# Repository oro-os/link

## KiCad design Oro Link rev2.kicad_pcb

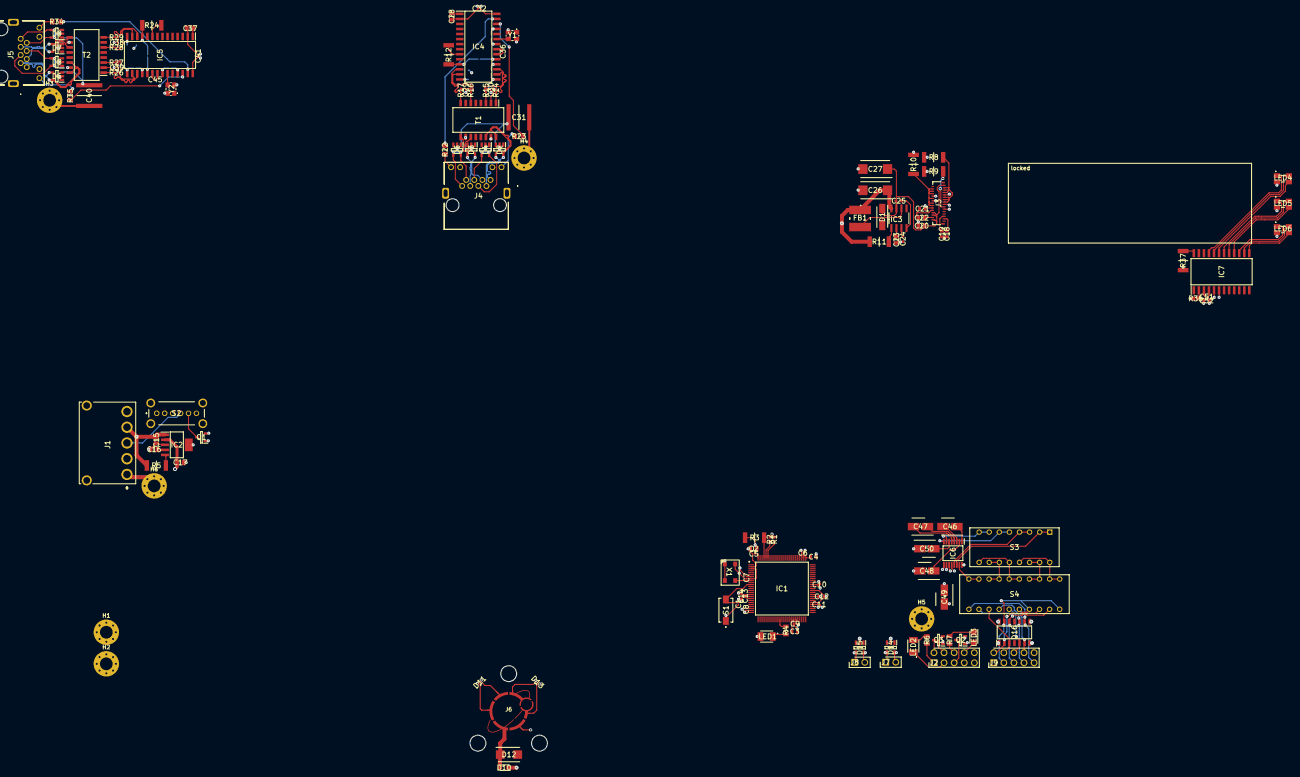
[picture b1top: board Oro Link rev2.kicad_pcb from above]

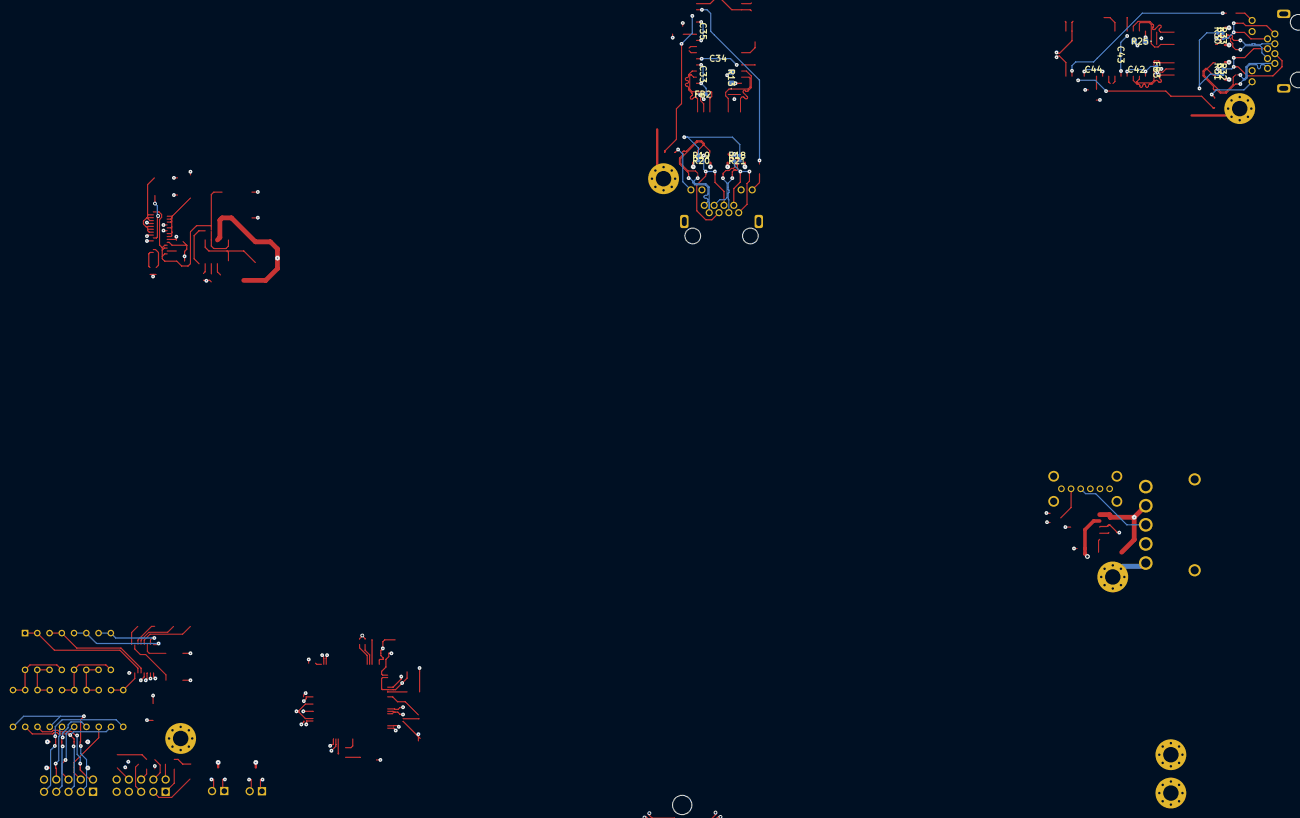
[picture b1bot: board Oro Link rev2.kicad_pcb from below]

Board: 4 copper layers, 148 parts (18 on the bottom side), 148 nets.

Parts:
C1, C5, C6, C7, C8, C9, C10, C11, C13, C29, C30, C32, C33, C34, C35, C36, C38, C39, C41, C42, C43, C44, C45, C51: 0.1u; CAPC0402X22N
C2, C20: 4.7u; CAPC2012X135N
C3, C4, C12: 2.2u; CAPC1608X90N
C14, C18, C19, C21, C52: 1u; CAPC1608X90N
C15, C16, C17, C28, C37: 10u; CAPC2012X135N
C22: 4,7u; CAPC2012X135N
C23: 0.01u; CAPC2012X75N
C24: 0.047u; C1608_Commercial_Tight
C25: 0.001u; C1608_Commercial_Tight
C26, C27: 33u; CAPPM7343X310N
C31, C40: 1nF 5kV; CAPC5664X270N
C46, C47, C48, C49, C50: 0.1u; CAPAE430X610N
D1: SS12; DIOM5227X250N
D2, D3, D4, D5, D6, D7, D8, D9, D14, D15: ESDS302DBVR; SOT95P280X145-5N
D10: RFU02VSM8STR; SODFL2514X80N
D11, D13: RCLAMP3552T.TNT; RCLAMP3552TTNT
D12: P6SMB15A-Q; DIOM5436X244N
D16: SMDA05C-8.TBT; SOIC127P600X175-14N
FB1: CD54NP-180MC; CD54NP180MC
FB2, FB3: BLM18BB600SZ1D; BLM18EG121SH1D
H1, H2, H3, H4, H5, H6: MountingHole_Pad; MountingHole_3.2mm_M3_Pad_Via
IC1: STM32F479VGT6; QFP50P1600X1600X160-100N
IC2: TPS73733DCQ; SOT127P706X180-6N
IC3: TPS6734IDR; SOIC127P600X175-8N
IC4, IC5: ENC28J60-I_SO; SOIC127P1030X265-28N
IC6: SN75C3232EPWR; SOP65P640X120-16N
IC7: IS31FL3218-GRLS2; SOIC127P1036X265-24N
J1: DF63-5P-3.96DS; DF635P396DS
J2, J9: 67996-110HLF; HDRV10W67P254_2X5_1270X483X858P
J3: 3-2328724-1; 323287241
J4, J5: SS-60300-103; SS60300103
J6: OroConn6p; OroConn6p_WithMounts
J7, J8: 10129378-902003BLF; HDRV2W67P0X254_1X2_508X241X1082P
LED1, LED2: AA3528VRVFS/A; AA3528VRVFSA
LED3: CLM3C-WKW-CXAYA453; CLM3CWKWCXAYA453
LED4, LED5, LED6: 150120M173000
Q1, Q2, Q3: PMV20ENR; SOT95P230X110-3N
R1, R2: 4.7k; RESC1005X40N
R3, R5, R8, R9, R10, R11, R12, R24, R37: 10k; RESC5025X65N
R4, R6, R7: 1k; RESC2012X60N
R13, R25: 2.32k, <=1%; ERJP06__0805_
R14, R15, R16, R17, R26, R27, R28, R29: RC1210FR-0749R9L; RESC0603X26N
R18, R19, R20, R21, R30, R31, R32, R33: 75R; RESC1005X40N
R22, R23, R34, R35: 470R; RESC2012X60N
R36: 3.3k; RESC1608X55N
S1: TL6400AF160QJ
S2: MSS225004
S3: 206-124; 206124
S4: 206-125; 206125
T1, T2: PT61017XPEL; SOIC127P930X570-16N
X1: 7P-26.000MBP-T
Y1, Y2: 25MHz; ASE24576MHZLCT

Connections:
+3V3: C2.1, C5.2, C6.2, C7.2, C8.2, C9.2, C10.2, C11.2, C12.1, C13.2, C14.2, C17.2, C21.2, C32.1, C35.1, C36.1, C41.1, C44.1, C45.1, C49.1, C51.1, C52.2, FB2.1, FB3.1, IC1.3 (VBAT), IC1.8 (VDD_1), IC1.17 (VREF+), IC1.18 (VDDA), IC1.24 (VDD_2), IC1.45 (VDD_3), IC1.55 (VDDDSI), IC1.56 (VCAPDSI), IC1.62 (VDD12DSI), IC1.65 (VDDUSB), IC1.77 (VDD_4), IC1.100 (VDD_5), IC2.2 (OUT), IC4.15 (VDDTX), IC4.19 (VDDRX), IC4.20 (VDDPLL), IC4.25 (VDDOSC), IC4.28 (VDD), IC5.15 (VDDTX), IC5.19 (VDDRX), IC5.20 (VDDPLL), IC5.25 (VDDOSC), IC5.28 (VDD), IC6.16 (VCC), IC7.3 (VCC), J3.12, J3.15, LED1.2, LED4.2 (A_G), LED5.2 (A_G), LED6.2 (A_G), R1.1, R2.1, R3.1, R9.2, R37.1, X1.6 (VCC), Y1.4 (VDD), Y2.4 (VDD)
+5V: C15.1, C26.1, D10.1, FB1.1, IC2.1 (IN), IC3.8 (VCC), J1.4, R5.1, R11.2, S2.1
/COM Bus Header/C1+: C46.1, IC6.1 (C1+)
/COM Bus Header/C1-: C46.2, IC6.3 (C1-)
/COM Bus Header/C2+: C47.1, IC6.4 (C2+)
/COM Bus Header/C2-: C47.2, IC6.5 (C2-)
/COM Bus Header/D_CTS: S3.9, S3.12, S4.C2, S4.C3
/COM Bus Header/D_RTS: S3.10, S3.11, S4.D2, S4.D3
/COM Bus Header/D_RX: S3.14, S3.15, S4.B2, S4.B3
/COM Bus Header/D_TX: S3.13, S3.16, S4.A2, S4.A3
/COM Bus Header/P2: D16.2 (I/O_1), J9.2, S4.B1
/COM Bus Header/P3: D16.13 (I/O_8), J9.3, S4.A1, S4.B4
/COM Bus Header/P4: D16.3 (I/O_2), J9.4, S4.D4
/COM Bus Header/P5: D16.12 (I/O_7), J9.5, S4.A4, S4.E1
/COM Bus Header/P6: D16.5 (I/O_3), J9.6, S4.C4
/COM Bus Header/P7: D16.10 (I/O_6), J9.7, S4.D1
/COM Bus Header/P8: D16.6 (I/O_4), J9.8, S4.C1
/COM Bus Header/P9: D16.9 (I/O_5), J9.9, S4.E4
/COM Bus Header/UART_CTS: IC1.87 (PD3), IC6.9 (ROUT2)
/COM Bus Header/UART_RTS: IC1.20 (PA1), IC6.10 (DIN2)
/COM Bus Header/UART_RX: IC1.22 (PA3), IC6.12 (ROUT1)
/COM Bus Header/UART_TX: IC1.21 (PA2), IC6.11 (DIN1)
/COM Bus Header/V+: C48.1, IC6.2 (V+)
/COM Bus Header/V-: C50.2, IC6.6 (V-)
/External Ethernet/CT_45: D8.4 (I/O1), D8.5 (I/O2), J5.4, J5.5, R32.1
/External Ethernet/CT_78: D9.4 (I/O1), D9.5 (I/O2), J5.7, J5.8, R33.1
/External Ethernet/GLED+: IC5.27 (LEDA), R34.2
/External Ethernet/RX+: D7.5 (I/O2), J5.3, T2.11 (RX+)
/External Ethernet/RX-: D7.4 (I/O1), J5.6, T2.9 (RX-)
/External Ethernet/SCK: IC1.41 (PB10), IC5.8 (SCK)
/External Ethernet/SDI: IC1.15 (PC3), IC5.7 (SI)
/External Ethernet/SDO: IC1.14 (PC2), IC5.6 (SO)
/External Ethernet/TPIN+: IC5.13 (TPIN+), R28.1, T2.6 (RD+)
/External Ethernet/TPIN-: IC5.12 (TPIN-), R29.1, T2.8 (RD-)
/External Ethernet/TPOUT+: IC5.17 (TPOUT+), R26.1, T2.1 (TD+)
/External Ethernet/TPOUT-: IC5.16 (TPOUT-), R27.1, T2.3 (TD-)
/External Ethernet/TX+: D6.4 (I/O1), J5.1, T2.16 (TX+)
/External Ethernet/TX-: D6.5 (I/O2), J5.2, T2.14 (TX-)
/External Ethernet/YLED+: IC5.26 (LEDB), R35.2
/External Ethernet/~INT: IC1.99 (PB9), IC5.4 (~INT)
/External Ethernet/~RST: IC1.4 (PC13), IC5.10 (~RESET)
/Front Panel Client/HDD+: J2.6, R7.1
/Front Panel Client/HDD-: J2.8, LED3.2
/Front Panel Client/PLED+: J2.1, R6.2
/Front Panel Client/PLED-: J2.3, LED2.1
/Front Panel Client/PWR+: J2.5, Q2.3
/Front Panel Client/PWR-: J2.7, Q2.2
/Front Panel Client/PWR_ON: IC1.50 (PD8), Q2.1
/Front Panel Client/RESET: IC1.49 (PB15), Q3.1
/Front Panel Client/RST+: J2.2, Q3.3
/Front Panel Client/RST-: J2.4, Q3.2
/Indicator Lights/O7: IC7.13 (O7), LED6.3 (K_G)
/Indicator Lights/O8: IC7.14 (O8), LED6.4 (K_R)
/Indicator Lights/O9: IC7.15 (O9), LED6.1 (K_B)
/Indicator Lights/O10: IC7.16 (O10), LED5.3 (K_G)
/Indicator Lights/O11: IC7.17 (O11), LED5.4 (K_R)
/Indicator Lights/O12: IC7.18 (O12), LED5.1 (K_B)
/Indicator Lights/O13: IC7.19 (O13), LED4.3 (K_G)
/Indicator Lights/O14: IC7.20 (O14), LED4.4 (K_R)
/Indicator Lights/O15: IC7.21 (O15), LED4.1 (K_B)
/Indicator Lights/SCL: IC1.95 (PB6), IC7.6 (SCL), R1.2
/Indicator Lights/SDA: IC1.96 (PB7), IC7.5 (SDA), R2.2
/Microcontroller/DBGUART_RX: D14.4 (I/O1), IC1.32 (PE7), J7.1
/Microcontroller/DBGUART_TX: D14.5 (I/O2), IC1.33 (PE8), J7.2
/Microcontroller/SYSETH_MISO: IC1.27 (PA6), IC4.6 (SO)
/Microcontroller/SYSETH_SCK: IC1.26 (PA5), IC4.8 (SCK)
/Microcontroller/SYSTEH_MOSI: IC1.28 (PA7), IC4.7 (SI)
/Microcontroller/SYSTEH_~INT: IC1.30 (PB1), IC4.4 (~INT)
/Microcontroller/SYSTEH_~RST: IC1.29 (PB0), IC4.10 (~RESET)
/Microcontroller/USB_D+: D15.5 (I/O2), IC1.74 (PA12), J8.2
/Microcontroller/USB_D-: D15.4 (I/O1), IC1.73 (PA11), J8.1
/Microcontroller/VCAP1: C3.1, IC1.43 (VCAP1)
/Microcontroller/VCAP2: C4.1, IC1.76 (VCAP2)
/OLED Socket/+12V: C20.1, C25.2, C27.1, D1.1, IC3.7 (FB), J3.2, J3.6, J3.8, J3.31
/OLED Socket/EXTCAP: C18.2, J3.3
/OLED Socket/EXTCAP2: C22.2, J3.4
/OLED Socket/EXTCAP3: C19.2, J3.5
/OLED Socket/SCK: IC1.81 (PC10), J3.22
/OLED Socket/SDI: IC1.90 (PD6), J3.23
/OLED Socket/~RST: IC1.89 (PD5), J3.18
/Power Supply/5VSB: J1.5, S2.2
/Power Supply/PSU_ON: J1.3, S2.4
/Power Supply/PW_OK: IC1.48 (PB14), J1.2
/Power Supply/PW_ON: IC1.47 (PB13), Q1.1
/SWD Pad/FLASH: D13.2, IC1.97 (BOOT0), J6.3, R3.2
/SWD Pad/SWCLK: D11.2, IC1.79 (PA14), J6.5
/SWD Pad/SWDIO: D11.1, IC1.75 (PA13), J6.6
/SWD Pad/SWO: D13.1, IC1.92 (PB3), J6.4
/SWD Pad/VCC: D10.2, D12.1, J6.1
/System Ethernet/CT_45: D4.4 (I/O1), D4.5 (I/O2), J4.4, J4.5, R20.1
/System Ethernet/CT_78: D5.4 (I/O1), D5.5 (I/O2), J4.7, J4.8, R21.1
/System Ethernet/GLED+: IC4.27 (LEDA), R22.2
/System Ethernet/RX+: D3.5 (I/O2), J4.3, T1.11 (RX+)
/System Ethernet/RX-: D3.4 (I/O1), J4.6, T1.9 (RX-)
/System Ethernet/TPIN+: IC4.13 (TPIN+), R16.1, T1.6 (RD+)
/System Ethernet/TPIN-: IC4.12 (TPIN-), R17.1, T1.8 (RD-)
/System Ethernet/TPOUT+: IC4.17 (TPOUT+), R14.1, T1.1 (TD+)
/System Ethernet/TPOUT-: IC4.16 (TPOUT-), R15.1, T1.3 (TD-)
/System Ethernet/TX+: D2.4 (I/O1), J4.1, T1.16 (TX+)
/System Ethernet/TX-: D2.5 (I/O2), J4.2, T1.14 (TX-)
/System Ethernet/YLED+: IC4.26 (LEDB), R23.2
GND: C1.2, C2.2, C3.2, C4.2, C5.1, C6.1, C7.1, C8.1, C9.1, C10.1, C11.1, C12.2, C13.1, C14.1, C15.2, C16.1, C17.1, C18.1, C19.1, C20.2, C21.1, C22.1, C23.1, C24.1, C26.2, C27.2, C28.1, C29.2, C30.2, C32.2, C35.2, C36.2, C37.1, C38.2, C39.2, C41.2, C44.2, C45.2, C48.2, C49.2, C50.1, C51.2, C52.1, H6.1, IC1.2 (VSS_1), IC1.7 (VSS_2), IC1.16 (VSSA), IC1.23 (VSS_3), IC1.44 (VSS_4), IC1.59 (VSSDSI), IC1.78 (VSS_5), IC2.3 (GND_1), IC2.6 (GND_2), IC3.5 (GND), IC4.2 (VSS), IC4.11 (VSSRX), IC4.18 (VSSTX), IC4.21 (VSSPLL), IC4.22 (VSSOSC), IC5.2 (VSS), IC5.11 (VSSRX), IC5.18 (VSSTX), IC5.21 (VSSPLL), IC5.22 (VSSOSC), IC6.15 (GND), IC7.4 (GND), J1.1, J3.10, J3.11, J4.10 (ANODE_YELLOW/CATHODE_GREEN_1), J4.11 (ANODE_GREEN/CATHODE_YELLOW_2), J5.10 (ANODE_YELLOW/CATHODE_GREEN_1), J5.11 (ANODE_GREEN/CATHODE_YELLOW_2), J6.2, Q1.2, R8.1, R10.1, R12.1, R13.2, R24.1, R25.2, R36.1, S1.1 (COM), S4.E2, S4.E3, X1.1 (GND/AFC), X1.3 (GND), Y1.2 (GND/CASE), Y2.2 (GND/CASE)
GNDPWR: C31.1, C40.1, D2.2 (GND), D3.2 (GND), D4.2 (GND), D5.2 (GND), D6.2 (GND), D7.2 (GND), D8.2 (GND), D9.2 (GND), D11.3, D12.2, D13.3, D14.2 (GND), D15.2 (GND), D16.1 (GND_1), D16.7 (GND_2), D16.8 (GND_3), D16.14 (GND_4), H1.1, H2.1, H3.1, H4.1, H5.1, J1.MH1, J1.MH2, J4.MH1, J4.MH2, J5.MH1, J5.MH2, S2.MH1, S2.MH2, S2.MH3, S2.MH4
unnamed: C29.1, R16.2, R17.2
unnamed: C31.2, R18.2, R19.2, R20.2, R21.2
unnamed: C38.1, R28.2, R29.2
unnamed: C40.2, R30.2, R31.2, R32.2, R33.2
unnamed: C1.1, IC1.11 (NRST), S1.2 (NO)
unnamed: IC1.37 (PE12), R4.1
unnamed: IC1.9 (PH0), X1.4 (CLK)
unnamed: IC2.5 (EN), R5.2
unnamed: C16.2, IC2.4 (NR/FB)
unnamed: C25.1, IC3.4 (COMP)
unnamed: IC3.1 (EN), R11.1
unnamed: D1.2, FB1.2, IC3.6 (OUT)
unnamed: C23.2, IC3.2 (REF)
unnamed: C24.2, IC3.3 (SS)
unnamed: IC4.23 (OSC1), Y1.3 (OUTPUT)
unnamed: IC4.14 (RBIAS), R13.1
unnamed: C28.2, IC4.1 (VCAP)
unnamed: IC4.9 (~CS), R12.2
unnamed: IC5.23 (OSC1), Y2.3 (OUTPUT)
unnamed: IC5.14 (RBIAS), R25.1
unnamed: C37.2, IC5.1 (VCAP)
unnamed: IC5.9 (~CS), R24.2
unnamed: IC6.14 (DOUT1), S3.1, S3.2
unnamed: IC6.7 (DOUT2), S3.7, S3.8
unnamed: IC6.13 (RIN1), S3.3, S3.4
unnamed: IC6.8 (RIN2), S3.5, S3.6
unnamed: IC7.2 (R_EXT), R36.2
unnamed: IC7.24 (~SDB), R37.2
unnamed: J3.13, R9.1
unnamed: J3.14, J3.16, J3.20, J3.24, J3.26, J3.28, R10.2
unnamed: J3.17, J3.19, J3.21, J3.25, J3.27, J3.29, R8.2
unnamed: J4.9 (ANODE_GREEN/CATHODE_YELLOW_1), R22.1
unnamed: J4.12 (ANODE_YELLOW/CATHODE_GREEN_2), R23.1
unnamed: J5.9 (ANODE_GREEN/CATHODE_YELLOW_1), R34.1
unnamed: J5.12 (ANODE_YELLOW/CATHODE_GREEN_2), R35.1
unnamed: LED1.1, R4.2
unnamed: LED2.2, R6.1
unnamed: LED3.1, R7.2
unnamed: Q1.3, S2.5
unnamed: C30.1, FB2.2, R14.2, R15.2, T1.2 (CT_1)
unnamed: R18.1, T1.10 (CT_3)
unnamed: R19.1, T1.15 (CT_4)
unnamed: C39.1, FB3.2, R26.2, R27.2, T2.2 (CT_1)
unnamed: R30.1, T2.10 (CT_3)
unnamed: R31.1, T2.15 (CT_4)

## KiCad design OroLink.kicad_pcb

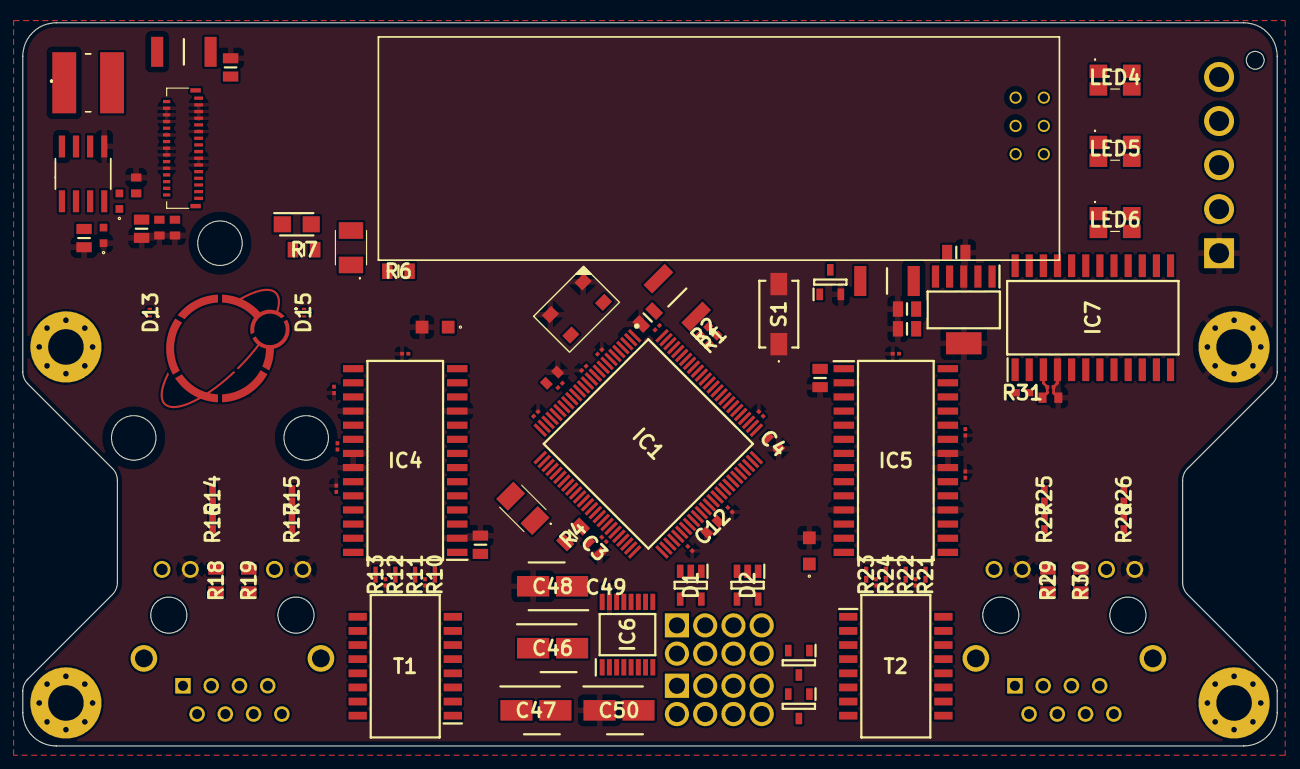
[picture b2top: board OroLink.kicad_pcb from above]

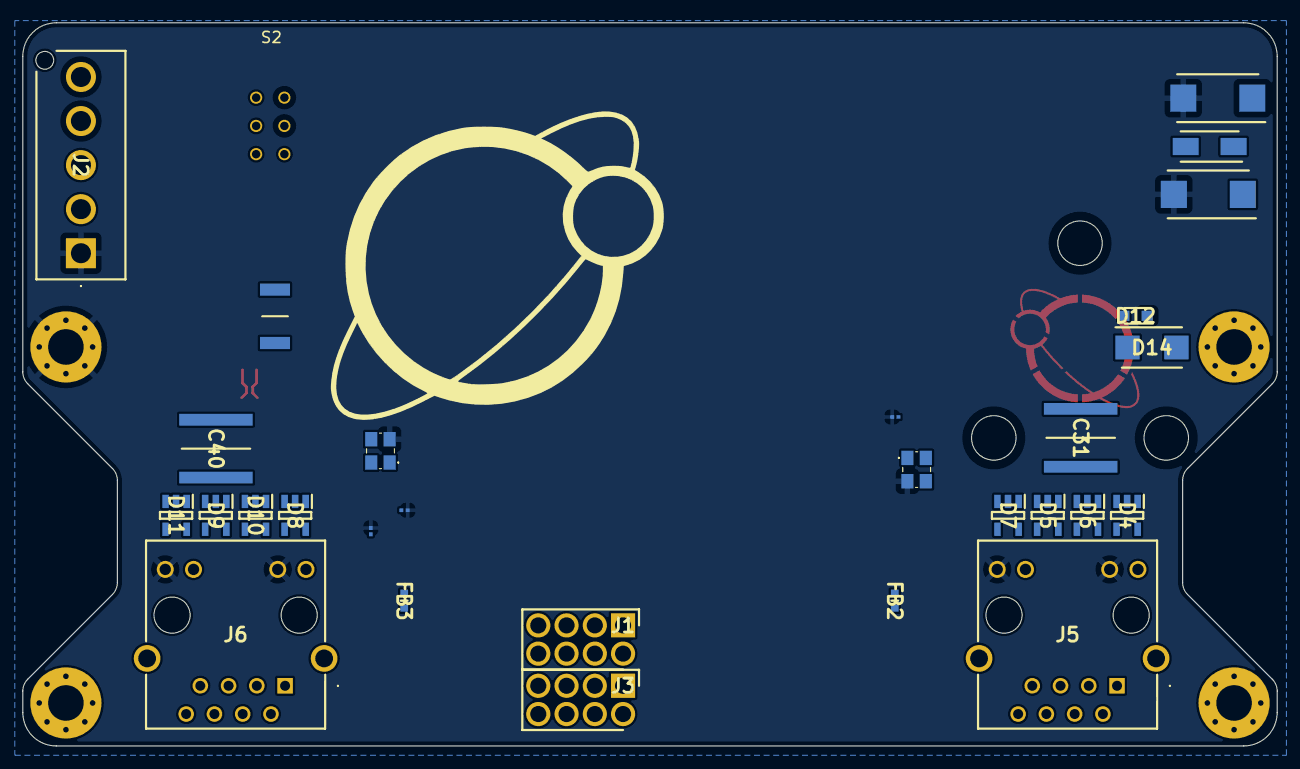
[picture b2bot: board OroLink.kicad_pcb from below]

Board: 4 copper layers, 112.8 x 65.0 mm, 136 parts (29 on the bottom side), 135 nets.

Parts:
C1, C5, C6, C7, C8, C9, C10, C11, C13, C29, C30, C32, C33, C34, C35, C36, C38, C39, C41, C42, C43, C44, C45, C49, C51: 0.1u; CAPC0402X22N
C2, C20, C22: 4.7u; CAPC2012X135N
C3, C4, C12: 2.2u; CAPC1608X90N
C14, C18, C19, C21, C52: 1u; CAPC1608X90N
C15, C16, C17, C28, C37: 10u; CAPC2012X135N
C23: 0.01u; CAPC2012X75N
C24: 0.047u; C1608_Commercial_Tight
C25: 0.001u; C1608_Commercial_Tight
C26, C27: 33u; CAPPM7343X310N
C31, C40: 1nF 5kV; CAPC5664X270N
C46, C47, C48, C50: 0.1u; CAPAE430X610N
D1, D2, D4, D5, D6, D7, D8, D9, D10, D11: ESDS302DBVR; SOT95P280X145-5N
D3: SS12; DIOM5227X250N
D12: RFU02VSM8STR; SODFL2514X80N
D13, D15: RCLAMP3552T.TNT; RCLAMP3552TTNT
D14: P6SMB15A-Q; DIOM5436X244N
FB1: CD54NP-180MC; CD54NP180MC
FB2, FB3: BLM18BB600SZ1D; BLM18EG121SH1D
H1, H2, H3, H4: MountingHole_Pad; MountingHole_3.2mm_M3_Pad_Via
IC1: STM32F479VGT6; QFP50P1600X1600X160-100N
IC2: TPS73733DCQ; SOT127P706X180-6N
IC3: TPS6734IDR; SOIC127P600X175-8N
IC4, IC5: ENC28J60-I_SO; SOIC127P1030X265-28N
IC6: SN75C3232EPWR; SOP65P640X120-16N
IC7: IS31FL3218-GRLS2; SOIC127P1036X265-24N
J1, J3: 67996-408HLF; HDRV8W89P254_2X4_1016X483X858P
J2: DF63-5P-3.96DSA; DF635P396DSA
J4: 3-2328724-1; 323287241
J5, J6: JXD2-0Z10NL; JXD20Z10NL
J7: OroConn6p; OroConn6p_WithMounts
LED1, LED2: AA3528VRVFS/A; AA3528VRVFSA
LED3: CLM3C-WKW-CXAYA453; CLM3CWKWCXAYA453
LED4, LED5, LED6: 150120M173000
Q1, Q2, Q3: PMV20ENR; SOT95P230X110-3N
R1, R2: 4.7k; RESC1005X40N
R3, R5, R8, R32: 10k; RESC5025X65N
R4, R6, R7: 1k; RESC2012X60N
R9, R20: 2.32k, <=1%; ERJP06__0805_
R10, R11, R12, R13, R21, R22, R23, R24: RMCF0201FT49R9; RESC0603X26N
R14, R15, R16, R17, R25, R26, R27, R28: 75R; RESC1005X40N
R18, R19, R29, R30: 470R; RESC2012X60N
R31: 5.6K; RESC1105X40N
S1: TL6400AF160QJ
S2: 25146NAH
T1, T2: PT61017XPEL; SOIC127P930X570-16N
X1: 7P-26.000MBP-T
Y1, Y2: 25MHz; ASE24576MHZLCT

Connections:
+3V3: C2.1, C5.2, C6.2, C7.2, C8.2, C9.2, C10.2, C11.2, C12.1, C13.2, C14.2, C17.2, C21.2, C32.1, C33.1, C34.1, C35.1, C36.1, C41.1, C42.1, C43.1, C44.1, C45.1, C49.1, C51.1, C52.2, FB2.1, FB3.1, IC1.3 (VBAT), IC1.8 (VDD_1), IC1.17 (VREF+), IC1.18 (VDDA), IC1.24 (VDD_2), IC1.45 (VDD_3), IC1.55 (VDDDSI), IC1.56 (VCAPDSI), IC1.62 (VDD12DSI), IC1.65 (VDDUSB), IC1.77 (VDD_4), IC1.100 (VDD_5), IC2.2 (OUT), IC4.15 (VDDTX), IC4.19 (VDDRX), IC4.20 (VDDPLL), IC4.25 (VDDOSC), IC4.28 (VDD), IC5.15 (VDDTX), IC5.19 (VDDRX), IC5.20 (VDDPLL), IC5.25 (VDDOSC), IC5.28 (VDD), IC6.16 (VCC), IC7.3 (VCC), J4.12, J4.15, LED1.2, LED4.2 (A_G), LED5.2 (A_G), LED6.2 (A_G), R1.1, R2.1, R3.1, R32.1, X1.6 (VCC), Y1.4 (VDD), Y2.4 (VDD)
+5V: C15.1, C26.1, D12.1, FB1.1, IC2.1 (IN), IC3.8 (VCC), J2.4, R5.1, R8.2, S2.2 (NO2)
/COM Bus Header/C1+: C46.1, IC6.1 (C1+)
/COM Bus Header/C1-: C46.2, IC6.3 (C1-)
/COM Bus Header/C2+: C47.1, IC6.4 (C2+)
/COM Bus Header/C2-: C47.2, IC6.5 (C2-)
/COM Bus Header/CTS: IC1.87 (PD3), IC6.9 (ROUT2)
/COM Bus Header/RS232_CTS: IC6.8 (RIN2), J1.6
/COM Bus Header/RS232_RTS: IC6.7 (DOUT2), J1.8
/COM Bus Header/RS232_RX: IC6.13 (RIN1), J1.2
/COM Bus Header/RS232_TX: IC6.14 (DOUT1), J1.4
/COM Bus Header/RTS: IC1.20 (PA1), IC6.10 (DIN2)
/COM Bus Header/RX: IC1.22 (PA3), IC6.12 (ROUT1)
/COM Bus Header/TX: IC1.21 (PA2), IC6.11 (DIN1)
/COM Bus Header/V+: C48.1, IC6.2 (V+)
/COM Bus Header/V-: C50.2, IC6.6 (V-)
/External Ethernet/CS: IC1.46 (PB12), IC5.9 (~CS)
/External Ethernet/CT_45: D10.4 (I/O1), D10.5 (I/O2), J6.4, J6.5, R27.1
/External Ethernet/CT_78: D11.4 (I/O1), D11.5 (I/O2), J6.7, J6.8, R28.1
/External Ethernet/GLED+: IC5.27 (LEDA), R30.2
/External Ethernet/RX+: D9.5 (I/O2), J6.3, T2.11 (RX+)
/External Ethernet/RX-: D9.4 (I/O1), J6.6, T2.9 (RX-)
/External Ethernet/SCK: IC1.41 (PB10), IC5.8 (SCK)
/External Ethernet/SDI: IC1.49 (PB15), IC5.7 (SI)
/External Ethernet/SDO: IC1.48 (PB14), IC5.6 (SO)
/External Ethernet/TPIN+: IC5.13 (TPIN+), R23.1, T2.6 (RD+)
/External Ethernet/TPIN-: IC5.12 (TPIN-), R24.1, T2.8 (RD-)
/External Ethernet/TPOUT+: IC5.17 (TPOUT+), R21.1, T2.1 (TD+)
/External Ethernet/TPOUT-: IC5.16 (TPOUT-), R22.1, T2.3 (TD-)
/External Ethernet/TX+: D8.5 (I/O2), J6.1, T2.16 (TX+)
/External Ethernet/TX-: D8.4 (I/O1), J6.2, T2.14 (TX-)
/External Ethernet/YLED+: IC5.26 (LEDB), R29.2
/External Ethernet/~INT: IC1.99 (PB9), IC5.4 (~INT)
/External Ethernet/~RST: IC1.4 (PC13), IC5.10 (~RESET)
/Front Panel Client/HDD+: J3.6, R7.1
/Front Panel Client/HDD-: J3.8, LED3.2
/Front Panel Client/PLED+: J3.1, R6.2
/Front Panel Client/PLED-: J3.3, LED2.1
/Front Panel Client/PWR+: J3.5, Q2.3
/Front Panel Client/PWR-: J3.7, Q2.2
/Front Panel Client/PWR_ON: IC1.50 (PD8), Q2.1
/Front Panel Client/RESET: IC1.51 (PD9), Q3.1
/Front Panel Client/RST+: J3.2, Q3.3
/Front Panel Client/RST-: J3.4, Q3.2
/Indicator Lights/O7: IC7.13 (O7), LED6.3 (K_G)
/Indicator Lights/O8: IC7.14 (O8), LED6.4 (K_R)
/Indicator Lights/O9: IC7.15 (O9), LED6.1 (K_B)
/Indicator Lights/O10: IC7.16 (O10), LED5.3 (K_G)
/Indicator Lights/O11: IC7.17 (O11), LED5.4 (K_R)
/Indicator Lights/O12: IC7.18 (O12), LED5.1 (K_B)
/Indicator Lights/O13: IC7.19 (O13), LED4.3 (K_G)
/Indicator Lights/O14: IC7.20 (O14), LED4.4 (K_R)
/Indicator Lights/O15: IC7.21 (O15), LED4.1 (K_B)
/Indicator Lights/SCL: IC1.95 (PB6), IC7.6 (SCL), R1.2
/Indicator Lights/SDA: IC1.96 (PB7), IC7.5 (SDA), R2.2
/Microcontroller/DBGUART_RX: D1.4 (I/O1), IC1.32 (PE7), J1.1
/Microcontroller/DBGUART_TX: D1.5 (I/O2), IC1.33 (PE8), J1.3
/Microcontroller/SYSETH_CS: IC1.25 (PA4), IC4.9 (~CS)
/Microcontroller/SYSETH_MISO: IC1.27 (PA6), IC4.6 (SO)
/Microcontroller/SYSETH_SCK: IC1.26 (PA5), IC4.8 (SCK)
/Microcontroller/SYSTEH_MOSI: IC1.28 (PA7), IC4.7 (SI)
/Microcontroller/SYSTEH_~INT: IC1.30 (PB1), IC4.4 (~INT)
/Microcontroller/SYSTEH_~RST: IC1.29 (PB0), IC4.10 (~RESET)
/Microcontroller/USB_D+: D2.5 (I/O2), IC1.74 (PA12), J1.7
/Microcontroller/USB_D-: D2.4 (I/O1), IC1.73 (PA11), J1.5
/Microcontroller/VCAP1: C3.1, IC1.43 (VCAP1)
/Microcontroller/VCAP2: C4.1, IC1.76 (VCAP2)
/OLED Socket/+12V: C20.1, C25.2, C27.1, D3.1, IC3.7 (FB), J4.2, J4.6, J4.8, J4.31
/OLED Socket/CS: IC1.80 (PA15), J4.17
/OLED Socket/DC: IC1.82 (PC11), J4.19
/OLED Socket/EXTCAP: C18.2, J4.3
/OLED Socket/EXTCAP2: C22.2, J4.4
/OLED Socket/EXTCAP3: C19.2, J4.5
/OLED Socket/SCK: IC1.81 (PC10), J4.22
/OLED Socket/SDI: IC1.83 (PC12), J4.23
/OLED Socket/~RST: IC1.84 (PD0), J4.18
/Power Supply/5VSB: J2.5, S2.4 (C)
/Power Supply/PSU_ON: J2.3, S2.1 (NO1)
/Power Supply/PW_OK: IC1.13 (PC1), J2.2
/Power Supply/PW_ON: IC1.14 (PC2), Q1.1
/SWD Pad/FLASH: D15.2, IC1.97 (BOOT0), J7.3, R3.2
/SWD Pad/SWCLK: D13.2, IC1.79 (PA14), J7.5
/SWD Pad/SWDIO: D13.1, IC1.75 (PA13), J7.6
/SWD Pad/SWO: D15.1, IC1.92 (PB3), J7.4
/SWD Pad/VCC: D12.2, D14.1, J7.1
/System Ethernet/CT_45: D6.4 (I/O1), D6.5 (I/O2), J5.4, J5.5, R16.1
/System Ethernet/CT_78: D7.4 (I/O1), D7.5 (I/O2), J5.7, J5.8, R17.1
/System Ethernet/GLED+: IC4.27 (LEDA), R19.2
/System Ethernet/RX+: D5.5 (I/O2), J5.3, T1.11 (RX+)
/System Ethernet/RX-: D5.4 (I/O1), J5.6, T1.9 (RX-)
/System Ethernet/TPIN+: IC4.13 (TPIN+), R12.1, T1.6 (RD+)
/System Ethernet/TPIN-: IC4.12 (TPIN-), R13.1, T1.8 (RD-)
/System Ethernet/TPOUT+: IC4.17 (TPOUT+), R10.1, T1.1 (TD+)
/System Ethernet/TPOUT-: IC4.16 (TPOUT-), R11.1, T1.3 (TD-)
/System Ethernet/TX+: D4.5 (I/O2), J5.1, T1.16 (TX+)
/System Ethernet/TX-: D4.4 (I/O1), J5.2, T1.14 (TX-)
/System Ethernet/YLED+: IC4.26 (LEDB), R18.2
GND: C1.2, C2.2, C3.2, C4.2, C5.1, C6.1, C7.1, C8.1, C9.1, C10.1, C11.1, C12.2, C13.1, C14.1, C15.2, C16.1, C17.1, C18.1, C19.1, C20.2, C21.1, C22.1, C23.1, C24.1, C26.2, C27.2, C28.1, C29.2, C30.2, C32.2, C33.2, C34.2, C35.2, C36.2, C37.1, C38.2, C39.2, C41.2, C42.2, C43.2, C44.2, C45.2, C48.2, C49.2, C50.1, C51.2, C52.1, H4.1, IC1.2 (VSS_1), IC1.7 (VSS_2), IC1.16 (VSSA), IC1.23 (VSS_3), IC1.44 (VSS_4), IC1.59 (VSSDSI), IC1.78 (VSS_5), IC2.3 (GND_1), IC2.6 (GND_2), IC3.5 (GND), IC4.2 (VSS), IC4.11 (VSSRX), IC4.18 (VSSTX), IC4.21 (VSSPLL), IC4.22 (VSSOSC), IC5.2 (VSS), IC5.11 (VSSRX), IC5.18 (VSSTX), IC5.21 (VSSPLL), IC5.22 (VSSOSC), IC6.15 (GND), IC7.4 (GND), J2.1, J4.10, J4.11, J4.13, J4.14, J4.16, J4.20, J4.21, J4.24, J4.25, J4.26, J4.27, J4.28, J4.29, J5.10 (K_YELLOW), J5.12 (K_GREEN), J6.10 (K_YELLOW), J6.12 (K_GREEN), J7.2, Q1.2, R9.2, R20.2, R31.1, S1.1 (COM), X1.1 (GND/AFC), X1.3 (GND), Y1.2 (GND/CASE), Y2.2 (GND/CASE)
GNDPWR: C31.1, C40.1, D1.2 (GND), D2.2 (GND), D4.2 (GND), D5.2 (GND), D6.2 (GND), D7.2 (GND), D8.2 (GND), D9.2 (GND), D10.2 (GND), D11.2 (GND), D13.3, D14.2, D15.3, H1.1, H2.1, H3.1, J5.MH1, J5.MH2, J6.MH1, J6.MH2
unnamed: C29.1, R12.2, R13.2
unnamed: C31.2, R14.2, R15.2, R16.2, R17.2
unnamed: C38.1, R23.2, R24.2
unnamed: C40.2, R25.2, R26.2, R27.2, R28.2
unnamed: LED2.2, R6.1
unnamed: LED3.1, R7.2
unnamed: C1.1, IC1.11 (NRST), S1.2 (NO)
unnamed: IC1.37 (PE12), R4.1
unnamed: IC1.9 (PH0), X1.4 (CLK)
unnamed: IC2.5 (EN), R5.2
unnamed: C16.2, IC2.4 (NR/FB)
unnamed: C25.1, IC3.4 (COMP)
unnamed: IC3.1 (EN), R8.1
unnamed: D3.2, FB1.2, IC3.6 (OUT)
unnamed: C23.2, IC3.2 (REF)
unnamed: C24.2, IC3.3 (SS)
unnamed: IC4.23 (OSC1), Y1.3 (OUTPUT)
unnamed: IC4.14 (RBIAS), R9.1
unnamed: C28.2, IC4.1 (VCAP)
unnamed: IC5.23 (OSC1), Y2.3 (OUTPUT)
unnamed: IC5.14 (RBIAS), R20.1
unnamed: C37.2, IC5.1 (VCAP)
unnamed: IC7.2 (R_EXT), R31.2
unnamed: IC7.24 (~SDB), R32.2
unnamed: J5.11 (A_GREEN), R19.1
unnamed: J5.9 (A_YELLOW), R18.1
unnamed: J6.11 (A_GREEN), R30.1
unnamed: J6.9 (A_YELLOW), R29.1
unnamed: LED1.1, R4.2
unnamed: Q1.3, S2.3 (C)
unnamed: C30.1, FB2.2, R10.2, R11.2, T1.2 (CT_1)
unnamed: R14.1, T1.10 (CT_3)
unnamed: R15.1, T1.15 (CT_4)
unnamed: C39.1, FB3.2, R21.2, R22.2, T2.2 (CT_1)
unnamed: R25.1, T2.10 (CT_3)
unnamed: R26.1, T2.15 (CT_4)
